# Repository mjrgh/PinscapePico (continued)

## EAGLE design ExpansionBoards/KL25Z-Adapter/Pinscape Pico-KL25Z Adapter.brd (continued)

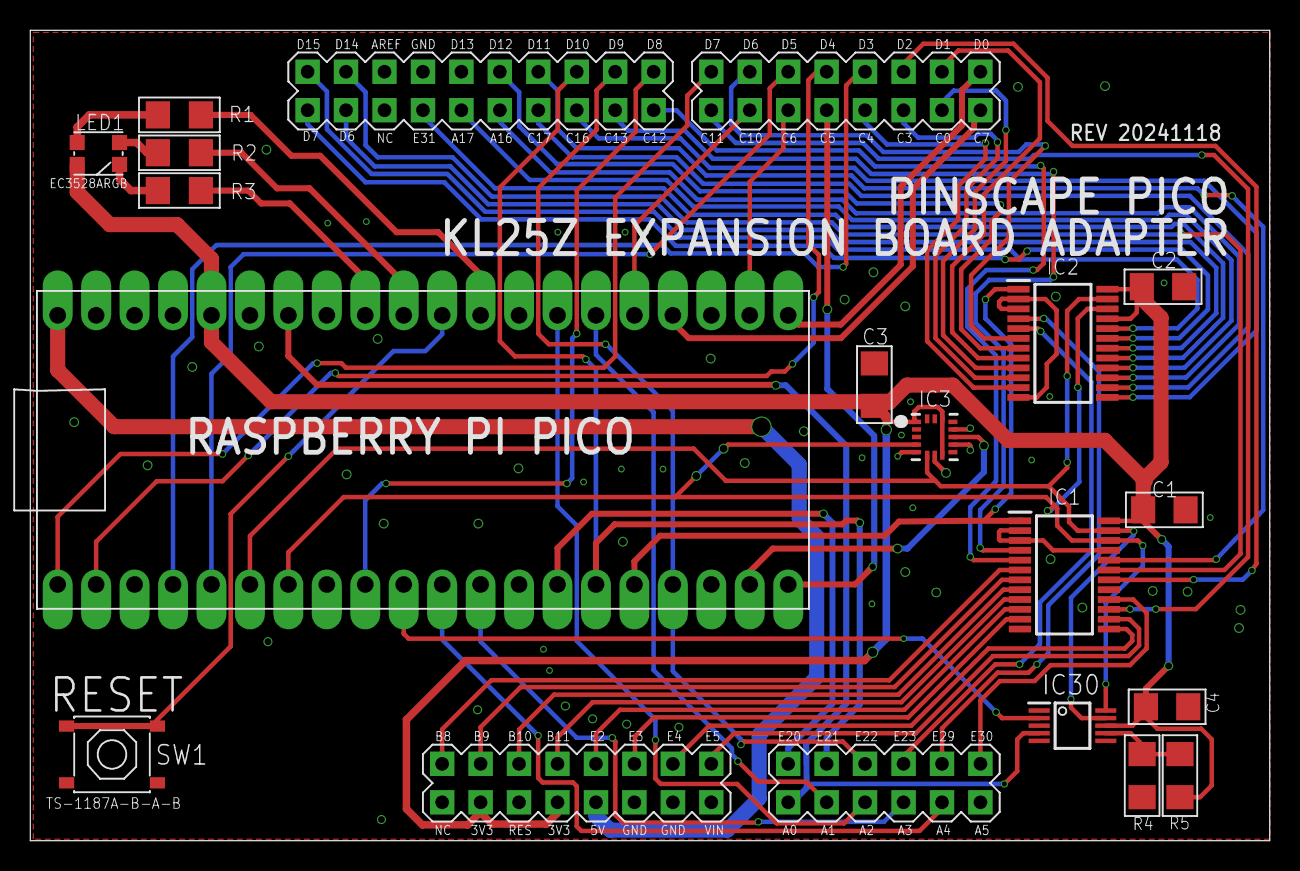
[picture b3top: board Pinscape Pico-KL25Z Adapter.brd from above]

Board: 2 copper layers, 81.9 x 53.5 mm, 17 parts (0 on the bottom side), 65 nets.
